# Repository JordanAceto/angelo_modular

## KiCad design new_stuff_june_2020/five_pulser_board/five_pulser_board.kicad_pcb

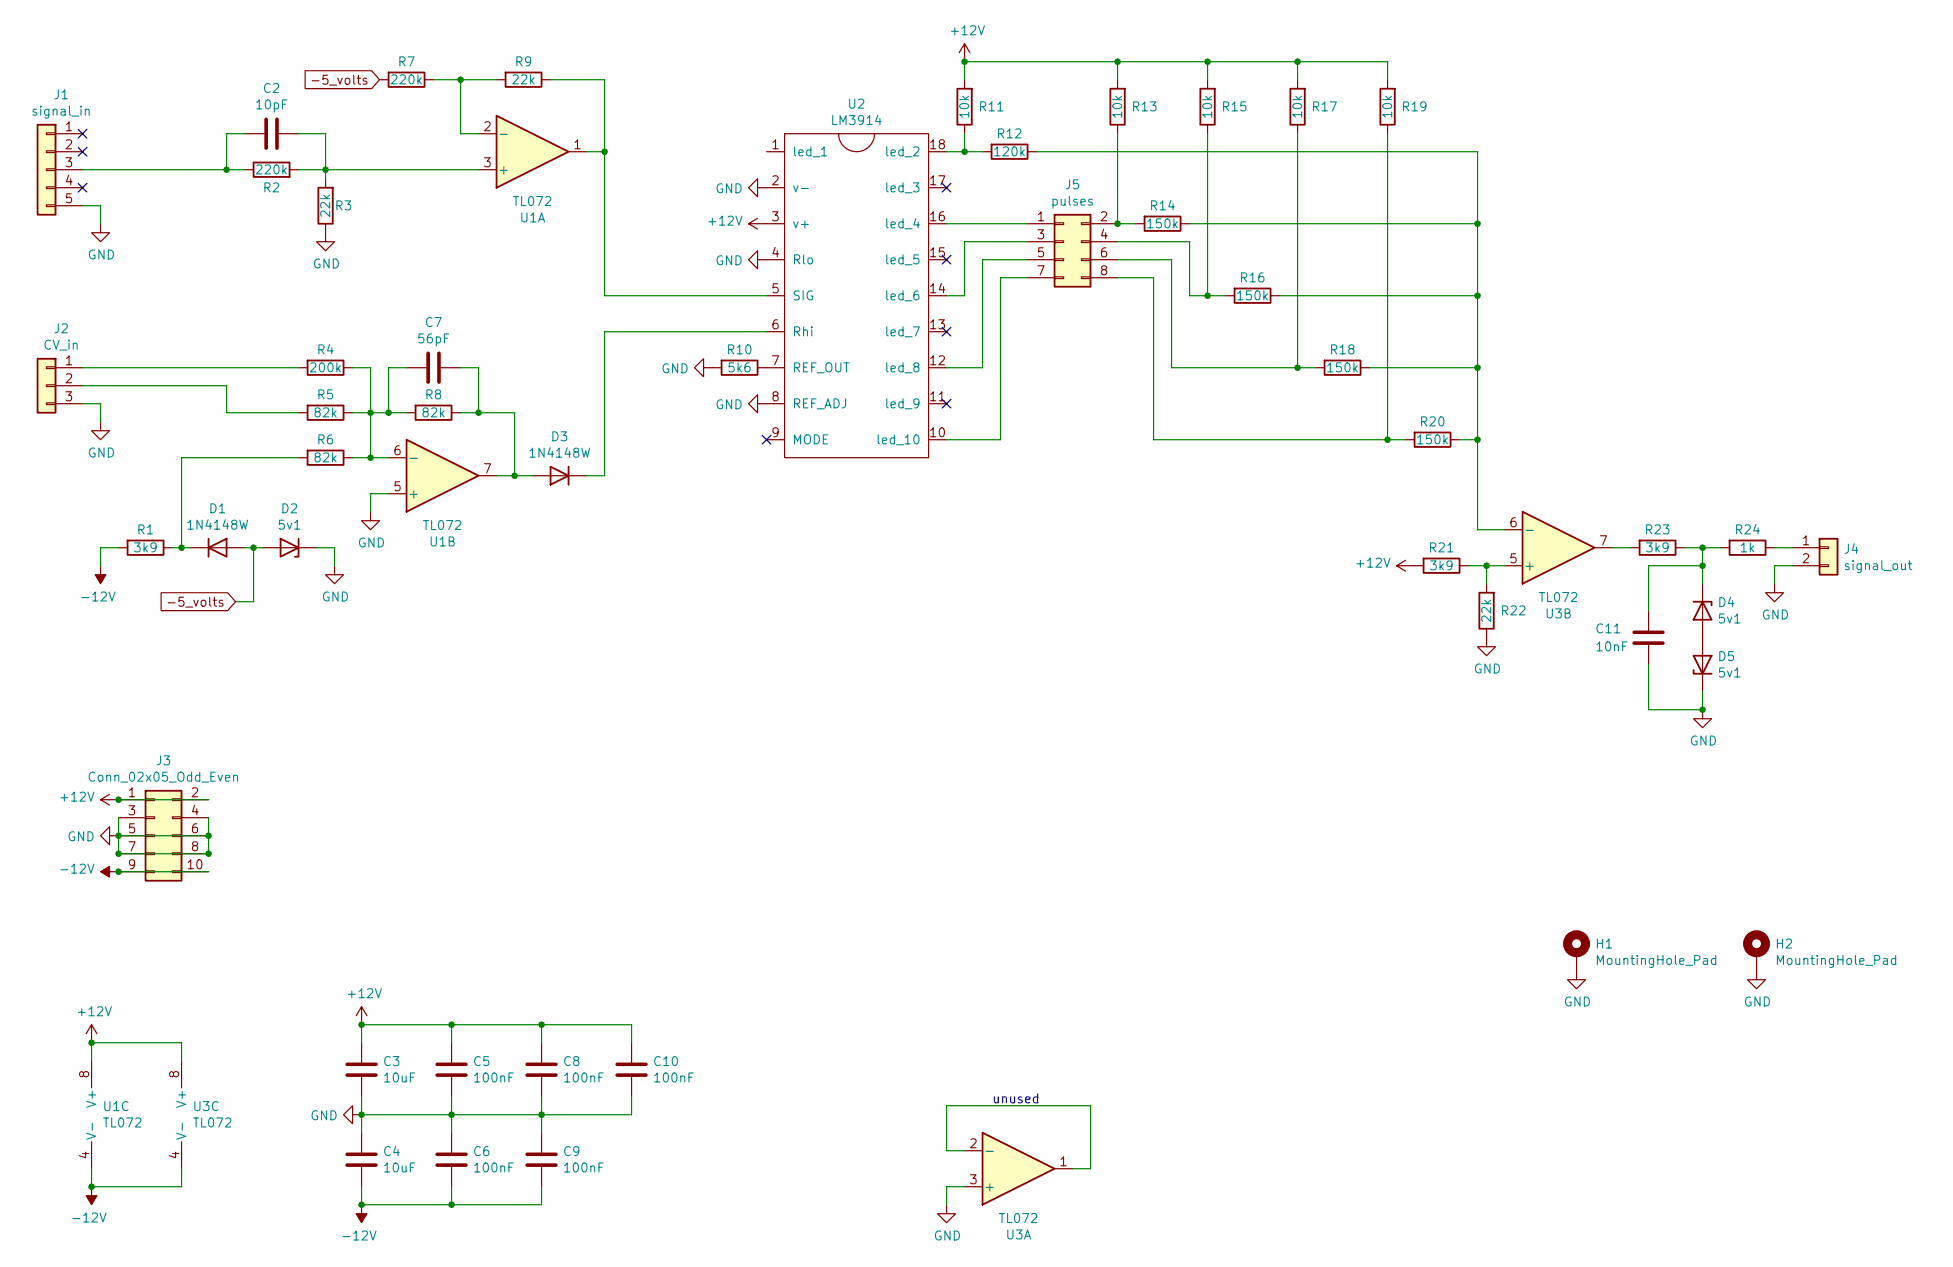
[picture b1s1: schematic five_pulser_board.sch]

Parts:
C2: 10pF; C_0805_2012Metric_Pad1.15x1.40mm_HandSolder
C3, C4: 10uF; C_0805_2012Metric_Pad1.15x1.40mm_HandSolder
C5, C6, C8, C9, C10: 100nF; C_0805_2012Metric_Pad1.15x1.40mm_HandSolder
C7: 56pF; C_0805_2012Metric_Pad1.15x1.40mm_HandSolder
C11: 10nF; C_0805_2012Metric_Pad1.15x1.40mm_HandSolder
D1, D3: 1N4148W; D_SOD-123
D2, D4, D5: 5v1; D_SOD-123
H1, H2: MountingHole_Pad; MountingHole_3.2mm_M3_Pad_Via
J1: signal_in; PinHeader_1x05_P2.54mm_Vertical
J2: CV_in; PinHeader_1x03_P2.54mm_Vertical
J3: Conn_02x05_Odd_Even; PinHeader_2x05_P2.54mm_Vertical
J4: signal_out; PinHeader_1x02_P2.54mm_Vertical
J5: pulses; PinHeader_2x04_P2.54mm_Vertical
R1, R21, R23: 3k9; R_0805_2012Metric_Pad1.15x1.40mm_HandSolder
R2, R7: 220k; R_0805_2012Metric_Pad1.15x1.40mm_HandSolder
R3, R9, R22: 22k; R_0805_2012Metric_Pad1.15x1.40mm_HandSolder
R4: 200k; R_0805_2012Metric_Pad1.15x1.40mm_HandSolder
R5, R6, R8: 82k; R_0805_2012Metric_Pad1.15x1.40mm_HandSolder
R10: 5k6; R_0805_2012Metric_Pad1.15x1.40mm_HandSolder
R11, R13, R15, R17, R19: 10k; R_0805_2012Metric_Pad1.15x1.40mm_HandSolder
R12: 120k; R_0805_2012Metric_Pad1.15x1.40mm_HandSolder
R14, R16, R18, R20: 150k; R_0805_2012Metric_Pad1.15x1.40mm_HandSolder
R24: 1k; R_0805_2012Metric_Pad1.15x1.40mm_HandSolder
U1, U3: TL072; SOIC-8_3.9x4.9mm_P1.27mm
U2: LM3914; DIP-18_W7.62mm

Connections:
+12V: C3.1, C5.1, C8.1, C10.1, J3.1, J3.2, R11.2, R13.2, R15.2, R17.2, R19.2, R21.2, U1.8 (V+), U2.3 (v+), U3.8 (V+)
-5_volts: D1.2 (A), D2.2 (A), R7.2
-12V: C4.2, C6.2, C9.2, J3.9, J3.10, R1.2, U1.4 (V-), U3.4 (V-)
GND: C3.2, C4.1, C5.2, C6.1, C8.2, C9.1, C10.2, C11.2, D2.1 (K), D5.1 (K), H1.1, H2.1, J1.5, J2.3, J3.3, J3.4, J3.5, J3.6, J3.7, J3.8, J4.2, R3.1, R10.2, R22.1, U1.5 (+), U2.2 (v-), U2.4 (Rlo), U2.8 (REF_ADJ), U3.3 (+)
unnamed: C2.1, R2.2, R3.2, U1.3 (+)
unnamed: C2.2, J1.3, R2.1
unnamed: C7.1, D3.2 (A), R8.1, U1.7
unnamed: C7.2, R4.1, R5.1, R6.1, R8.2, U1.6 (-)
unnamed: C11.1, D4.1 (K), R23.1, R24.2
unnamed: D1.1 (K), R1.1, R6.2
unnamed: D3.1 (K), U2.6 (Rhi)
unnamed: D4.2 (A), D5.2 (A)
unnamed: J2.1, R4.2
unnamed: J2.2, R5.2
unnamed: J4.1, R24.1
unnamed: J5.1, U2.16 (led_4)
unnamed: J5.2, R13.1, R14.2
unnamed: J5.3, U2.14 (led_6)
unnamed: J5.4, R15.1, R16.2
unnamed: J5.5, U2.12 (led_8)
unnamed: J5.6, R17.1, R18.2
unnamed: J5.7, U2.10 (led_10)
unnamed: J5.8, R19.1, R20.2
unnamed: R7.1, R9.2, U1.2 (-)
unnamed: R9.1, U1.1, U2.5 (SIG)
unnamed: R10.1, U2.7 (REF_OUT)
unnamed: R11.1, R12.2, U2.18 (led_2)
unnamed: R12.1, R14.1, R16.1, R18.1, R20.1, U3.6 (-)
unnamed: R21.1, R22.2, U3.5 (+)
unnamed: R23.2, U3.7
unnamed: U3.1, U3.2 (-)

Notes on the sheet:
unused

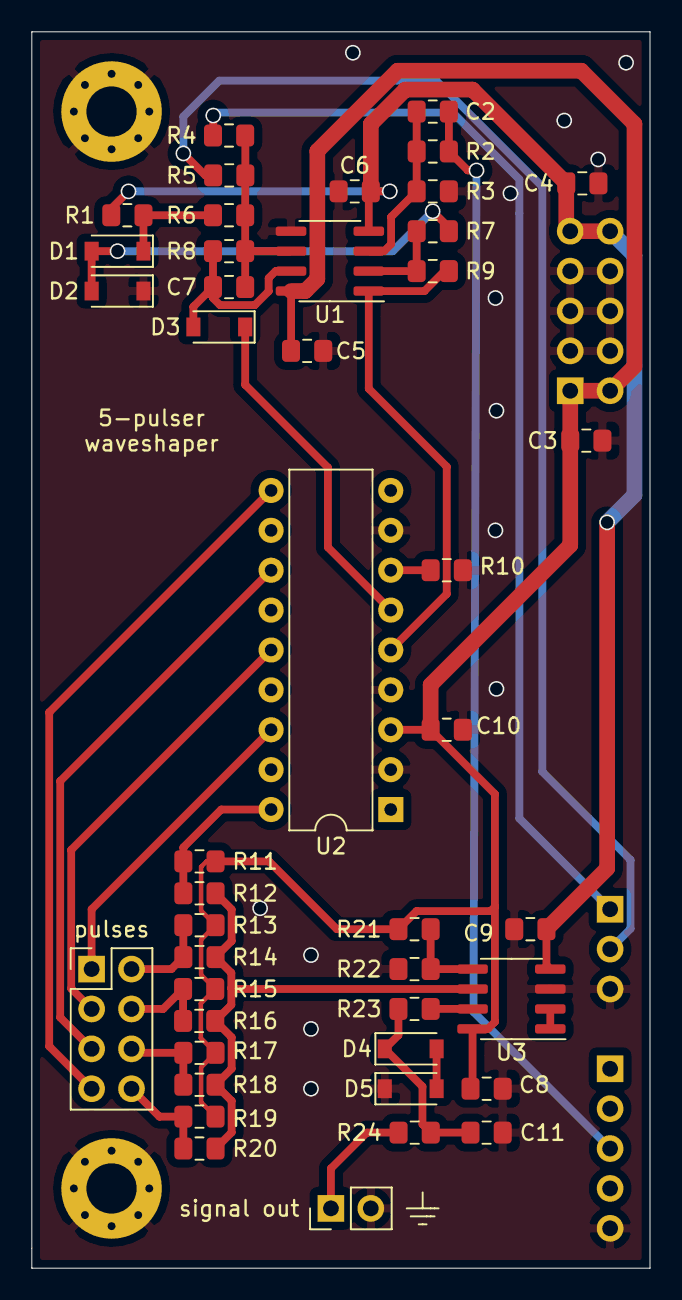
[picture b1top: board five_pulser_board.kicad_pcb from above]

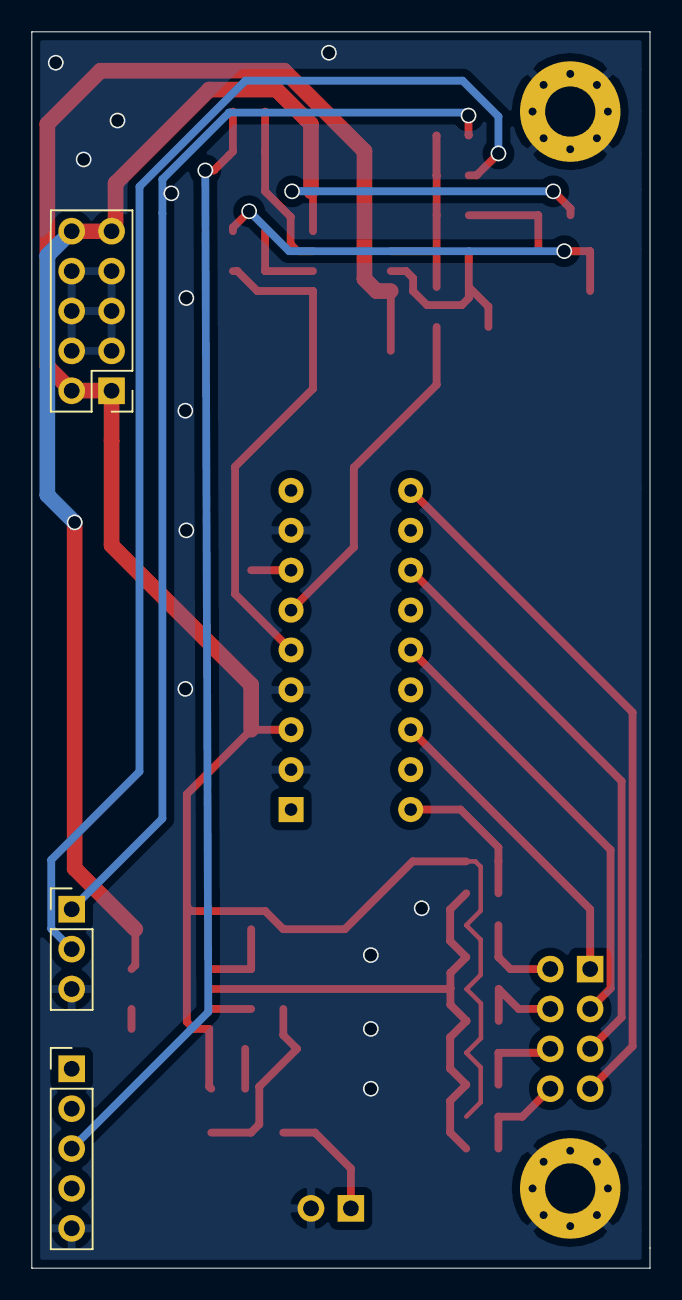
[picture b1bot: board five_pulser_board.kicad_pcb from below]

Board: 2 copper layers, 39.4 x 78.7 mm, 49 parts (3 on the bottom side), 31 nets.

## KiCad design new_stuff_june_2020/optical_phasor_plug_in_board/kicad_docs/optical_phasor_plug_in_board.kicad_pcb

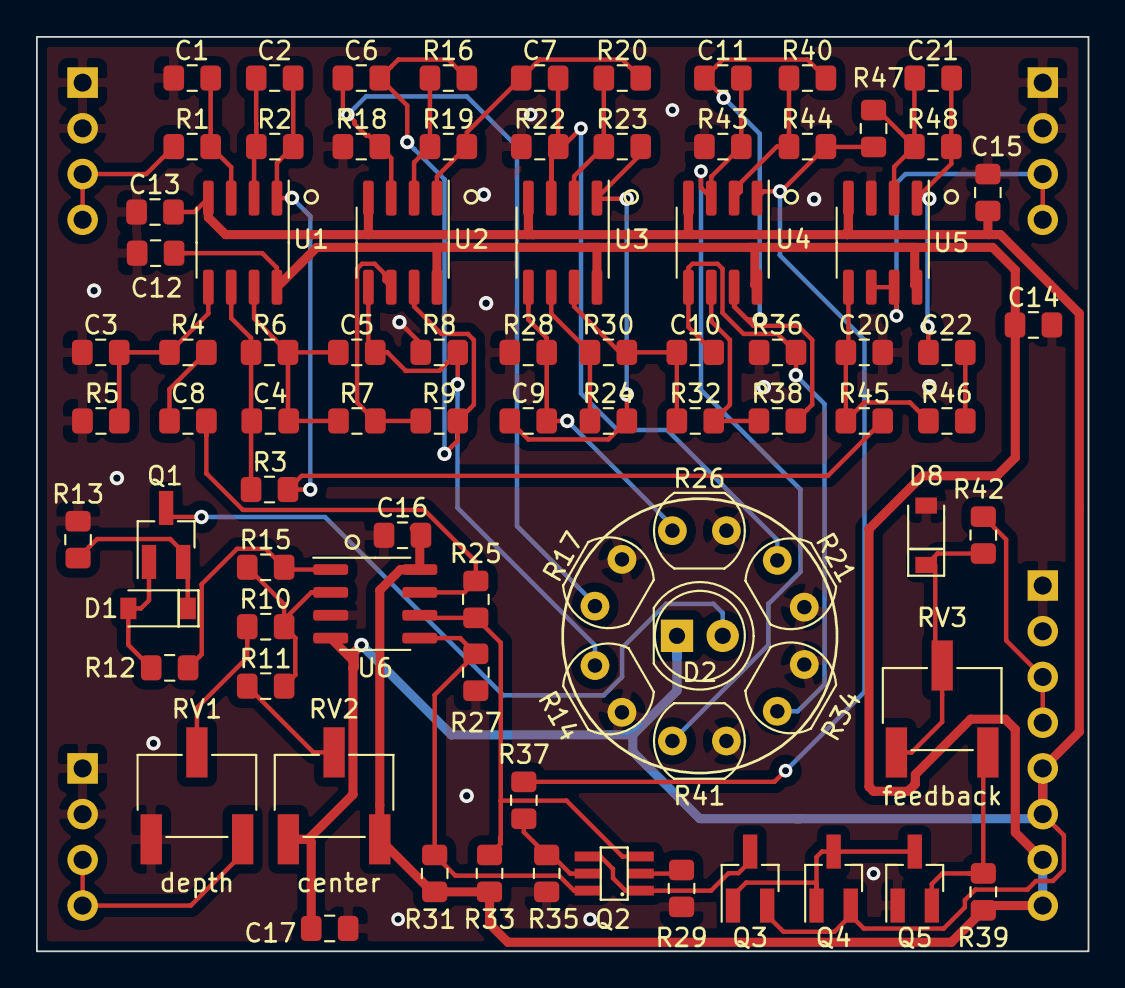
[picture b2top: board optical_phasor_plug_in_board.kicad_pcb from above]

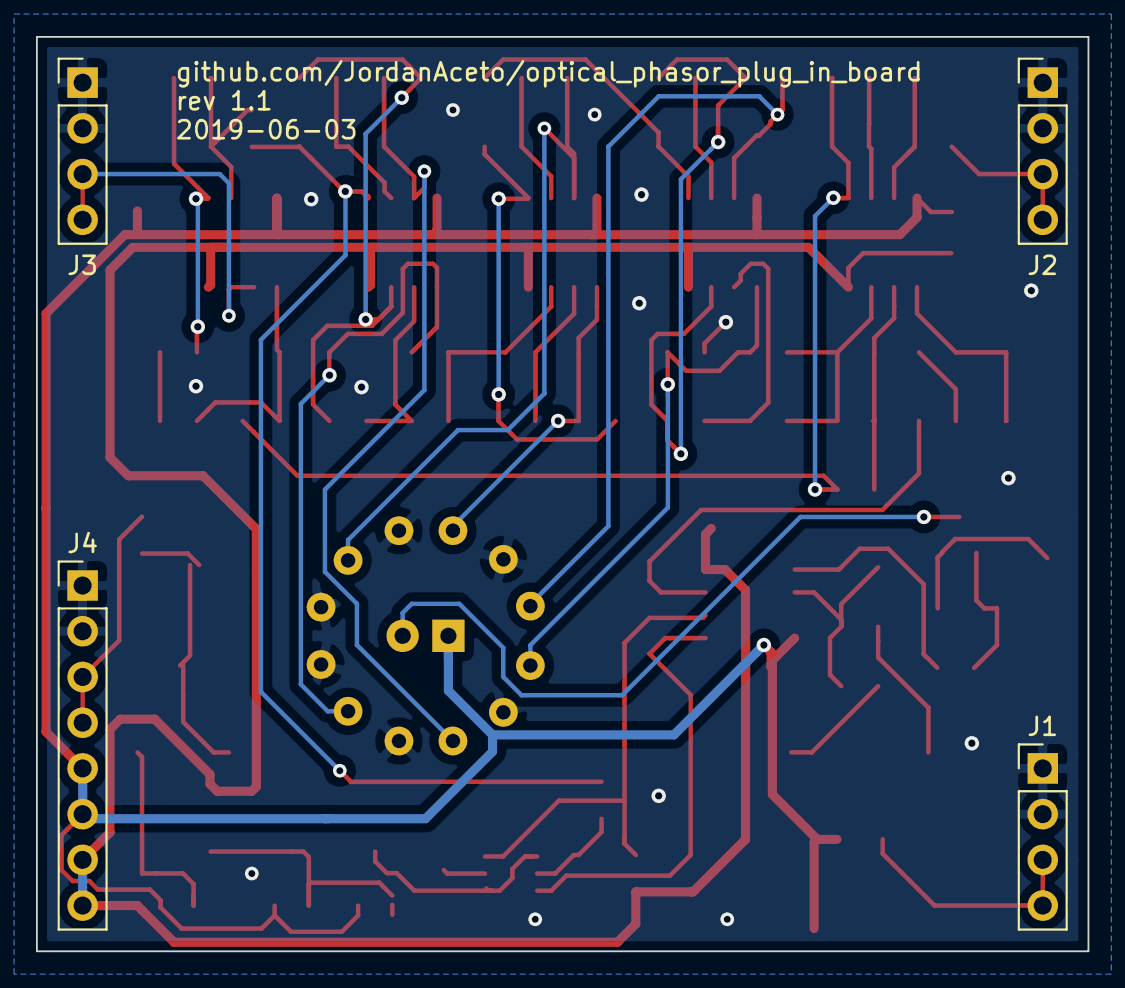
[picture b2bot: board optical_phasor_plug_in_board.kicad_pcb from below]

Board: 2 copper layers, 58.4 x 50.8 mm, 89 parts (4 on the bottom side), 52 nets.

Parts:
C1: 33pF; C_0805_2012Metric_Pad1.15x1.40mm_HandSolder
C2, C12, C13, C14, C15, C16, C17: 100nF; C_0805_2012Metric_Pad1.15x1.40mm_HandSolder
C3: 3n3; C_0805_2012Metric_Pad1.15x1.40mm_HandSolder
C4: 1nF; C_0805_2012Metric_Pad1.15x1.40mm_HandSolder
C5, C6, C7, C9, C10, C11: 6n8; C_0805_2012Metric_Pad1.15x1.40mm_HandSolder
C8: 470nF; C_0805_2012Metric_Pad1.15x1.40mm_HandSolder
C20: 470pF; C_0805_2012Metric_Pad1.15x1.40mm_HandSolder
C21: 1n; C_0805_2012Metric_Pad1.15x1.40mm_HandSolder
C22: 220nF; C_0805_2012Metric_Pad1.15x1.40mm_HandSolder
D1: 1N914; D_SOD-123
D2: green_diffused; LED_D5.0mm
D8: 1N5225B; D_SOD-123
J1, J2, J3: Conn_01x04_Male; PinHeader_1x04_P2.54mm_Vertical
J4: Conn_01x08_Male; PinHeader_1x08_P2.54mm_Vertical
Q1, Q5: MMBT3906; SOT-23_Handsoldering
Q2: BCM847DS135; SOT457
Q3, Q4: MMBT3904; SOT-23_Handsoldering
R1: 3k9; R_0805_2012Metric_Pad1.15x1.40mm_HandSolder
R2: 390k; R_0805_2012Metric_Pad1.15x1.40mm_HandSolder
R3, R6, R7, R9, R16, R19, R20, R23, R24, R30, R32, R38, R40, R44, R46, R47, R48: 4k7; R_0805_2012Metric_Pad1.15x1.40mm_HandSolder
R4: 8k2; R_0805_2012Metric_Pad1.15x1.40mm_HandSolder
R5, R8, R18, R22, R25, R27, R28, R36, R43: 220k; R_0805_2012Metric_Pad1.15x1.40mm_HandSolder
R10, R11, R13, R15: ???; R_0805_2012Metric_Pad1.15x1.40mm_HandSolder
R12: 10k; R_0805_2012Metric_Pad1.15x1.40mm_HandSolder
R14, R17, R21, R26, R34, R41: LDR; R_LDR_5.0x4.1mm_P3mm_Vertical
R29, R35: 220R; R_0805_2012Metric_Pad1.15x1.40mm_HandSolder
R31, R33: 47k; R_0805_2012Metric_Pad1.15x1.40mm_HandSolder
R37: 100k; R_0805_2012Metric_Pad1.15x1.40mm_HandSolder
R39: 680k; R_0805_2012Metric_Pad1.15x1.40mm_HandSolder
R42: 7k5; R_0805_2012Metric_Pad1.15x1.40mm_HandSolder
R45: 12k; R_0805_2012Metric_Pad1.15x1.40mm_HandSolder
RV1: 10k; Potentiometer_Bourns_3269W_Vertical
RV2: 100k; Potentiometer_Bourns_3269W_Vertical
RV3: 50k; Potentiometer_Bourns_3269W_Vertical
U1, U2, U3, U4, U5: RC4558; SOIC-8_3.9x4.9mm_P1.27mm
U6: TL072; SOIC-8_3.9x4.9mm_P1.27mm

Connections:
+12V: C12.1, C14.1, C16.1, J4.7, J4.8, R31.2, R33.2, R39.1, RV2.3, U1.8, U2.8, U3.8, U4.8, U5.8, U6.8
-12V: C13.1, C15.1, C17.1, D2.1, J4.5, J4.6, Q3.2, Q4.2, RV2.1, U1.4, U2.4, U3.4, U4.4, U5.4, U6.4
GND: C1.2, C3.2, C12.2, C13.2, C14.2, C15.2, C16.2, C17.2, C20.1, D8.2, J1.1, J1.2, J2.1, J2.2, J3.1, J3.2, J4.1, J4.2, Q5.1, R5.1, R8.1, R13.2, R14.2, R17.2, R18.1, R21.2, R22.1, R26.2, R27.1, R28.1, R29.1, R34.2, R35.1, R36.1, R41.2, R43.1, RV1.1, U5.3, U6.3
unnamed: C1.1, R1.2, U1.3
unnamed: C2.1, R2.1, R3.2, R45.2, U1.1
unnamed: C2.2, R2.2, U1.2
unnamed: C3.1, R4.2, R5.2, U1.5
unnamed: C4.1, R3.1, R6.2, U1.6
unnamed: C4.2, C5.2, R6.1, R7.2, U1.7
unnamed: C5.1, R8.2, R14.1, U2.5
unnamed: C6.1, R17.1, R18.2, U2.3
unnamed: C6.2, R9.1, R16.2, U2.7
unnamed: C7.1, R21.1, R22.2, U3.3
unnamed: C7.2, R19.1, R20.2, U2.1
unnamed: C8.1, R4.1
unnamed: C8.2, R25.1, U6.7
unnamed: C9.1, R26.1, R28.2, U3.5
unnamed: C9.2, R23.1, R24.2, U3.1
unnamed: C10.1, R34.1, R36.2, U4.5
unnamed: C10.2, R30.1, R32.2, U3.7
unnamed: C11.1, R41.1, R43.2, U4.3
unnamed: C11.2, R38.1, R40.2, U4.7
unnamed: C20.2, R45.1, R46.1, U5.5
unnamed: C21.1, C22.2, R48.1, U5.1
unnamed: C21.2, R47.1, R48.2, U5.2
unnamed: C22.1, R46.2
unnamed: D1.1, Q1.2, R13.1
unnamed: D1.2, Q1.1, R12.1
unnamed: D2.2, Q1.3
unnamed: D8.1, R42.1, RV3.1, RV3.2
unnamed: J1.3, J1.4, RV1.3
unnamed: J2.3, J2.4, R1.1
unnamed: J3.3, J3.4, U5.6, U5.7
unnamed: J4.3, J4.4, R42.2
unnamed: Q2.1, Q2.4, Q3.3
unnamed: Q2.2, R29.2
unnamed: Q2.3, R25.2, R33.1, U6.6
unnamed: Q2.5, R35.2, R37.1
unnamed: Q2.6, R27.2, R31.1, U6.5
unnamed: Q3.1, Q4.1, Q4.3, Q5.3
unnamed: Q5.2, R39.2, RV3.3
unnamed: R7.1, R9.2, U2.6
unnamed: R10.1, R11.1, R15.2, U6.2
unnamed: R10.2, RV1.2
unnamed: R11.2, RV2.2
unnamed: R12.2, R15.1, U6.1
unnamed: R16.1, R19.2, U2.2
unnamed: R20.1, R23.2, U3.2
unnamed: R24.1, R30.2, U3.6
unnamed: R32.1, R38.2, U4.6
unnamed: R37.2, R44.1, R47.2, U4.1
unnamed: R40.1, R44.2, U4.2

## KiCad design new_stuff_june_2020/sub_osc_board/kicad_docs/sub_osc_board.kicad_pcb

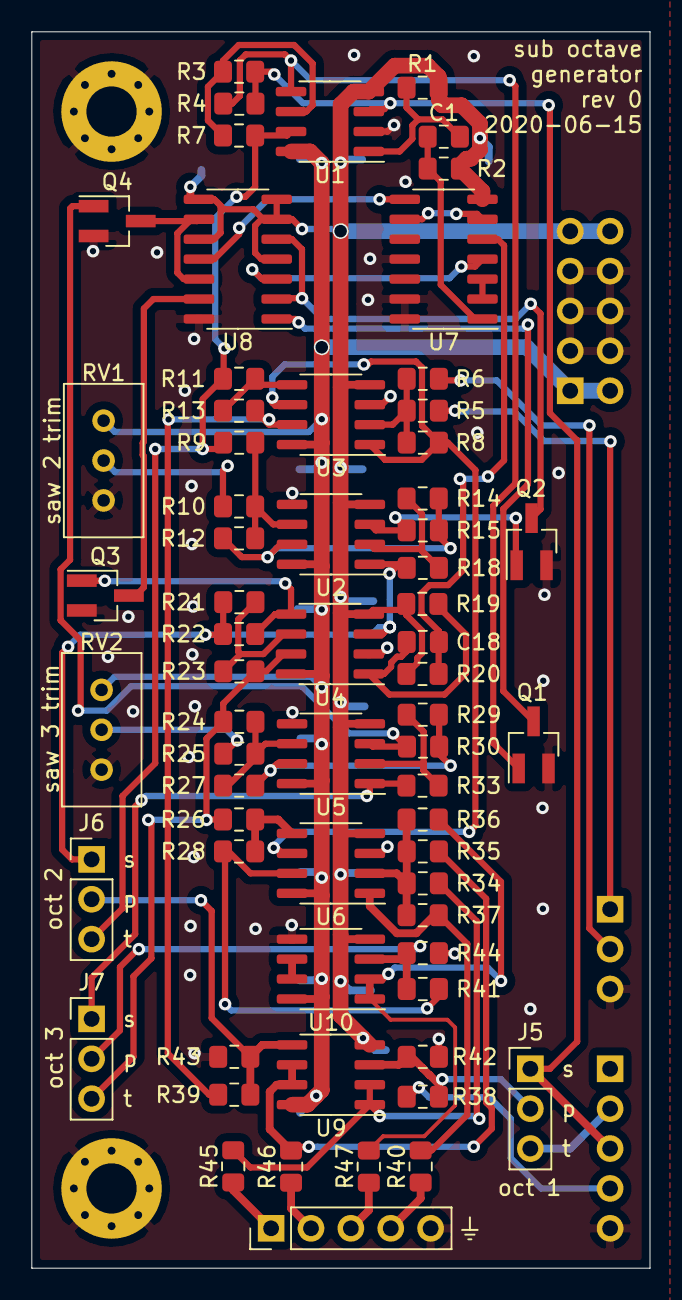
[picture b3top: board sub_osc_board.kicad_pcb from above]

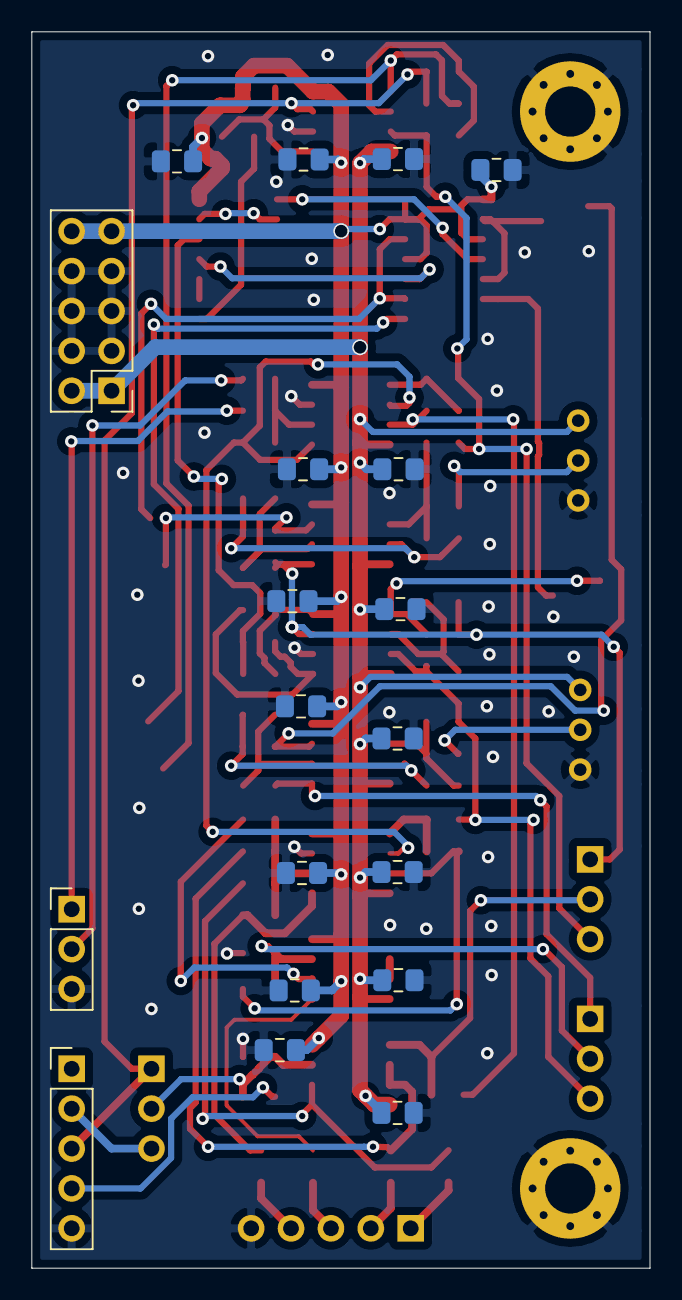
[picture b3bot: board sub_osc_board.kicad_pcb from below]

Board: 2 copper layers, 39.4 x 78.7 mm, 86 parts (19 on the bottom side), 57 nets.

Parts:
C1, C18: 1nF; C_0805_2012Metric_Pad1.15x1.40mm_HandSolder
C2, C3, C4, C5, C6, C7, C8, C9, C10, C11, C12, C13, C14, C15: 100nF; C_0805_2012Metric_Pad1.15x1.40mm_HandSolder
C16, C17: 10uF; C_0805_2012Metric_Pad1.15x1.40mm_HandSolder
H1, H2: MountingHole_Pad; MountingHole_3.2mm_M3_Pad_Via
J1: signal_inputs; PinHeader_1x05_P2.54mm_Vertical
J2: pwm_inputs; PinHeader_1x03_P2.54mm_Vertical
J3: power_input; PinHeader_2x05_P2.54mm_Vertical
J4: signal_outputs; PinHeader_1x05_P2.54mm_Vertical
J5, J6, J7: Conn_01x03; PinHeader_1x03_P2.54mm_Vertical
Q1, Q2, Q3, Q4: MMBF5457; SOT-23_Handsoldering
R1, R19: 10k; R_0805_2012Metric_Pad1.15x1.40mm_HandSolder
R2, R20: 22k; R_0805_2012Metric_Pad1.15x1.40mm_HandSolder
R3, R4, R6, R7, R9, R10, R14, R15, R18, R21, R22, R23, R24, R25, R29, R30, R33, R34, R35, R36, R37, R43, R44: 100k; R_0805_2012Metric_Pad1.15x1.40mm_HandSolder
R5: 330k; R_0805_2012Metric_Pad1.15x1.40mm_HandSolder
R8: 150k; R_0805_2012Metric_Pad1.15x1.40mm_HandSolder
R11, R26: 2k2; R_0805_2012Metric_Pad1.15x1.40mm_HandSolder
R12, R27: 51k; R_0805_2012Metric_Pad1.15x1.40mm_HandSolder
R13, R28: 2M2; R_0805_2012Metric_Pad1.15x1.40mm_HandSolder
R38, R39, R41: 120k; R_0805_2012Metric_Pad1.15x1.40mm_HandSolder
R40, R45, R46, R47: 1k; R_0805_2012Metric_Pad1.15x1.40mm_HandSolder
R42: dnf; R_0805_2012Metric_Pad1.15x1.40mm_HandSolder
RV1, RV2: 100k; Potentiometer_Bourns_3296W_Vertical
U1, U2, U3, U4, U5, U6, U9, U10: TL072; SOIC-8_3.9x4.9mm_P1.27mm
U7: 40106; SOIC-14_3.9x8.7mm_P1.27mm
U8: 4013; SOIC-14_3.9x8.7mm_P1.27mm

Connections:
+12V: C4.1, C6.1, C8.1, C10.1, C12.1, C14.1, C16.1, J3.1, J3.2, RV1.1, RV2.1, U1.8, U2.8, U3.8, U4.8, U5.8, U6.8, U9.8, U10.8
-12V: C2.2, C3.2, C5.2, C7.2, C9.2, C11.2, C13.2, C15.2, C17.2, J3.9, J3.10, R1.2, R2.2, R19.2, R20.2, U1.4, U2.4, U3.4, U4.4, U5.4, U6.4, U7.7, U8.4, U8.6, U8.7, U8.8, U8.10, U9.4, U10.4
/base_oct_out: R34.2, R45.2, U9.1, U9.2
/mix_out: R37.1, R40.2, U6.1
/pulse_in: J1.4, R38.2
/pulse_over_2: R13.1, R39.2, U3.7
/pulse_over_4: R28.1, R41.2, U6.7
/saw_in: J1.3, J5.1, R3.2, R4.2, U1.3
/saw_over_2: J6.1, R18.1, R21.2, R22.2, U2.1, U4.3
/saw_over_4: J7.1, R33.1, U5.1
/sub_oct_1_out: R35.2, R46.2, U9.6, U9.7
/sub_oct_2_out: R36.2, R47.2, U10.1, U10.2
/sub_osc_1/man_pw_in_1: J2.1, R5.2
/sub_osc_1/pwm_in_1: J2.2, R6.2
/sub_osc_1/summed_PWM: R8.1, U3.1, U3.6, U6.6
/tri_in: J1.2, J5.3
/tri_over_2: J6.3, R7.1, R9.2, R11.2, U1.7
/tri_over_4: J7.3, R23.1, R24.2, R26.2, U4.7
GND: C2.1, C3.1, C4.2, C5.1, C6.2, C7.1, C8.2, C9.1, C10.2, C11.1, C12.2, C13.1, C14.2, C15.1, C16.2, C17.1, H1.1, H2.1, J1.5, J2.3, J3.3, J3.4, J3.5, J3.6, J3.7, J3.8, J4.5, Q1.2, Q2.2, Q3.2, Q4.2, R42.2, R43.2, R44.2, RV1.3, RV2.3, U1.2, U2.5, U3.3, U4.2, U5.5, U6.3, U7.11, U7.13, U7.14, U8.14, U10.5
unnamed: C1.1, R2.1, U7.1
unnamed: C1.2, R1.1, U1.1
unnamed: C18.1, R20.1, U7.5
unnamed: C18.2, R19.1, U4.1
unnamed: J4.1, R45.1
unnamed: J4.2, R46.1
unnamed: J4.3, R47.1
unnamed: J4.4, R40.1
unnamed: J5.2, R38.1, R42.1, U9.3
unnamed: J6.2, R39.1, R43.1, U9.5
unnamed: J7.2, R41.1, R44.1, U10.3
unnamed: Q1.1, R4.1, U1.5
unnamed: Q1.3, U8.1
unnamed: Q2.1, R15.1, U2.3
unnamed: Q2.3, U8.2, U8.5
unnamed: Q3.1, R22.1, U4.5
unnamed: Q3.3, U8.13
unnamed: Q4.1, R30.1, U5.3
unnamed: Q4.3, U8.9, U8.12
unnamed: R3.1, R7.2, U1.6
unnamed: R5.1, R6.1, R8.2, U3.2
unnamed: R9.1, R10.1, R12.2, U2.6
unnamed: R10.2, RV1.2
unnamed: R11.1, R13.2, U3.5
unnamed: R12.1, R14.2, R15.2, U2.7
unnamed: R14.1, R18.2, U2.2
unnamed: R21.1, R23.2, U4.6
unnamed: R24.1, R25.1, R27.2, U5.6
unnamed: R25.2, RV2.2
unnamed: R26.1, R28.2, U6.5
unnamed: R27.1, R29.2, R30.2, U5.7
unnamed: R29.1, R33.2, U5.2
unnamed: R34.1, R35.1, R36.1, R37.2, U6.2
unnamed: U7.2, U7.3
unnamed: U7.4, U8.3
unnamed: U7.6, U7.9
unnamed: U7.8, U8.11
unnamed: U10.6, U10.7

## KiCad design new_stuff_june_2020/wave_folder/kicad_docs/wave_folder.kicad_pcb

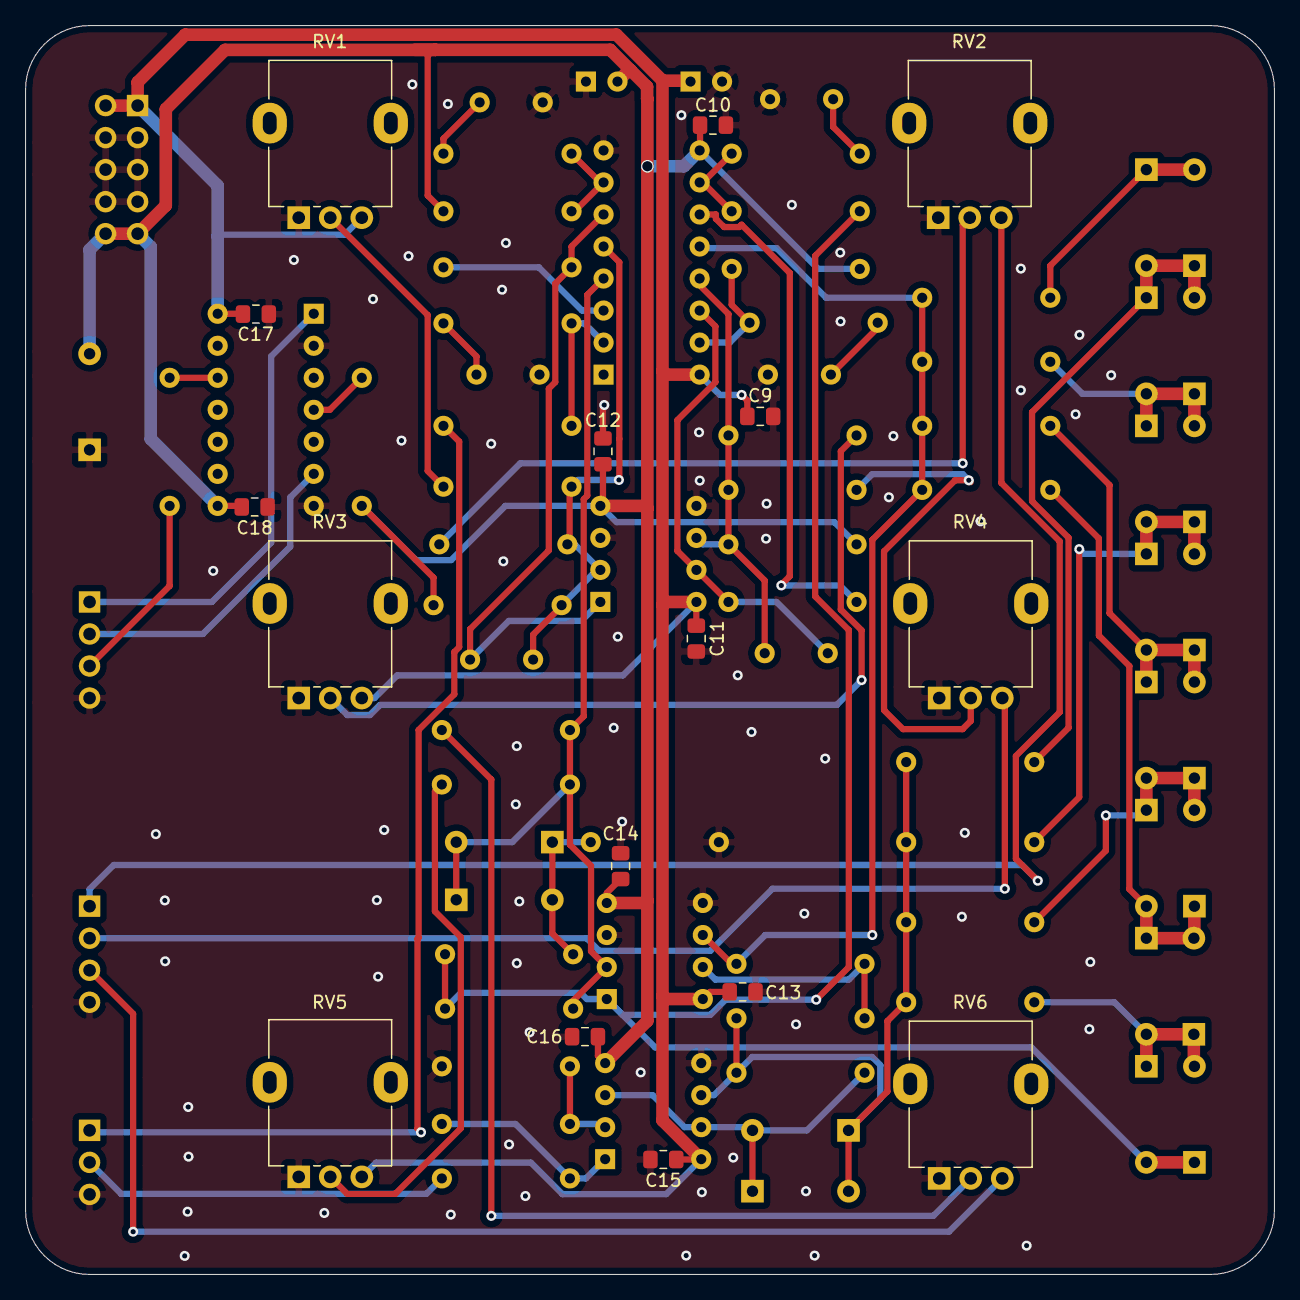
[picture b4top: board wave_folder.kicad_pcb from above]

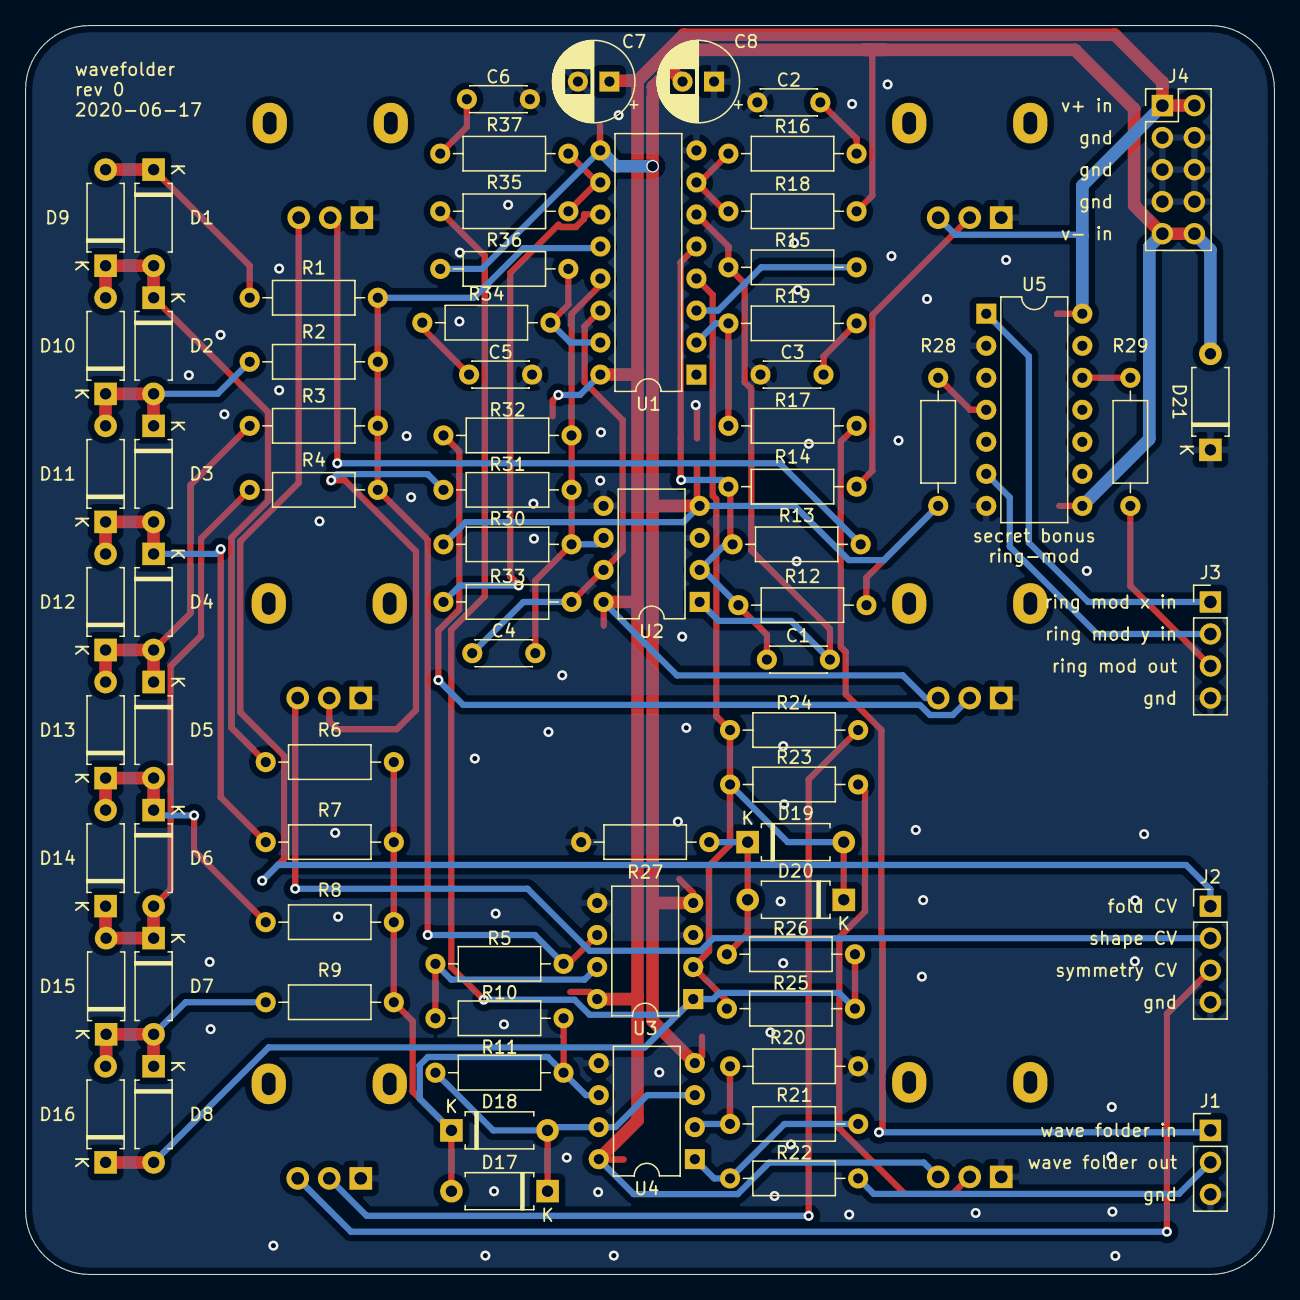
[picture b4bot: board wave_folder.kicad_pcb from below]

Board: 2 copper layers, 99.1 x 99.1 mm, 91 parts (75 on the bottom side), 50 nets.

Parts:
C1, C4: 100pF; C_Disc_D4.3mm_W1.9mm_P5.00mm
C2, C3, C5, C6: 560pF; C_Disc_D4.3mm_W1.9mm_P5.00mm
C7, C8: 10uF; CP_Radial_D6.3mm_P2.50mm
C9, C10, C11, C12, C13, C14, C15, C16, C17, C18: 100nF; C_0805_2012Metric_Pad1.15x1.40mm_HandSolder
D1, D2, D3, D4, D5, D6, D7, D8, D9, D10, D11, D12, D13, D14, D15, D16, D17, D18, D19, D20: D; D_A-405_P7.62mm_Horizontal
D21: D_Schottky; D_A-405_P7.62mm_Horizontal
J1: signal_port; PinHeader_1x03_P2.54mm_Vertical
J2: CV_port; PinHeader_1x04_P2.54mm_Vertical
J3: ring_mod_port; PinHeader_1x04_P2.54mm_Vertical
J4: power_in_connector; PinHeader_2x05_P2.54mm_Vertical
R1, R2, R3, R4, R6, R7, R8, R9: 15k; R_Axial_DIN0207_L6.3mm_D2.5mm_P10.16mm_Horizontal
R5, R10, R28: 5k6; R_Axial_DIN0207_L6.3mm_D2.5mm_P10.16mm_Horizontal
R11, R21: 56k; R_Axial_DIN0207_L6.3mm_D2.5mm_P10.16mm_Horizontal
R12, R30: 10M; R_Axial_DIN0207_L6.3mm_D2.5mm_P10.16mm_Horizontal
R13, R17, R24, R31: 100k; R_Axial_DIN0207_L6.3mm_D2.5mm_P10.16mm_Horizontal
R14, R23, R32: 220k; R_Axial_DIN0207_L6.3mm_D2.5mm_P10.16mm_Horizontal
R15, R33: 4k7; R_Axial_DIN0207_L6.3mm_D2.5mm_P10.16mm_Horizontal
R16, R19, R34, R37: 510; R_Axial_DIN0207_L6.3mm_D2.5mm_P10.16mm_Horizontal
R18, R36: 240k; R_Axial_DIN0207_L6.3mm_D2.5mm_P10.16mm_Horizontal
R20: 7k5; R_Axial_DIN0207_L6.3mm_D2.5mm_P10.16mm_Horizontal
R22, R29: 1k; R_Axial_DIN0207_L6.3mm_D2.5mm_P10.16mm_Horizontal
R25: 180k; R_Axial_DIN0207_L6.3mm_D2.5mm_P10.16mm_Horizontal
R26: 33k; R_Axial_DIN0207_L6.3mm_D2.5mm_P10.16mm_Horizontal
R27: 2k7; R_Axial_DIN0207_L6.3mm_D2.5mm_P10.16mm_Horizontal
R35: 27k; R_Axial_DIN0207_L6.3mm_D2.5mm_P10.16mm_Horizontal
RV1, RV2, RV3, RV4, RV5, RV6: 100k; Potentiometer_Alpha_RD901F-40-00D_Single_Vertical
U1: SSM2164; DIP-16_W7.62mm
U2, U3, U4: TL072; DIP-8_W7.62mm
U5: AD534; DIP-14_W7.62mm

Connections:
+12V: C7.1, C9.1, C11.1, C13.1, C15.1, C17.1, J4.1, J4.2, RV1.3, RV3.3, RV5.3, U1.16, U2.8, U3.8, U4.8, U5.14
-12V: C8.2, C10.2, C12.2, C14.2, C16.2, C18.2, D21.2, J4.9, J4.10, R12.2, R18.1, R28.2, R30.2, R36.1, U1.9, U2.4, U3.4, U4.4, U5.8
/core/core_i_in: R1.2, R2.2, R3.2, R4.2, R5.2, U1.12, U3.6
/core/core_out: D17.1, D18.2, R11.1, U4.3, U4.7
/core/core_v_in: D8.2, D16.1, R25.1, R26.1, R35.2, U3.1
/folds_CV: R13.2, RV2.2
/folds_CV_in: J2.1, RV2.3
/folds_VCA/folds_VCA_signal_i_out: D19.2, D20.1, R23.1, R24.1, R25.2, U1.4, U3.2
/manual_folds: R14.2, RV1.2
/manual_shape: R32.2, RV3.2
/manual_symmetry: R23.2, RV5.2
/ring_mod_out: J3.3, R29.1
/ring_mod_x_in: J3.1, U5.1
/ring_mod_y_in: J3.2, U5.6
/shape_CV: R31.2, RV4.2
/shape_CV_in: J2.2, RV4.3
/signal_in: J1.1, R17.2
/signal_out: J1.2, R22.2
/symmetry_CV: R24.2, RV6.2
/symmetry_CV_in: J2.3, RV6.3
GND: C2.2, C3.2, C5.2, C6.2, C7.2, C8.1, C9.2, C10.1, C11.2, C12.1, C13.2, C14.1, C15.2, C16.1, C17.2, C18.1, D21.1, J1.3, J2.4, J3.4, J4.3, J4.4, J4.5, J4.6, J4.7, J4.8, R20.1, R27.2, RV1.1, RV2.1, RV3.1, RV4.1, RV5.1, RV6.1, U1.8, U2.3, U2.5, U3.3, U3.5, U4.5, U5.2, U5.7
unnamed: C1.1, R15.2, U1.6, U2.1
unnamed: C1.2, R12.1, R13.1, R14.1, U1.5, U2.2
unnamed: C2.1, R16.1
unnamed: C3.1, R19.1
unnamed: C4.1, R33.2, U1.14, U2.7
unnamed: C4.2, R30.1, R31.1, R32.1, U1.13, U2.6
unnamed: C5.1, R34.1
unnamed: C6.1, R37.1
unnamed: D1.1, D9.2, R1.1
unnamed: D1.2, D2.1, D9.1, D10.2, R6.2
unnamed: D2.2, D3.1, D10.1, D11.2, R2.1
unnamed: D3.2, D4.1, D11.1, D12.2, R7.2
unnamed: D4.2, D5.1, D12.1, D13.2, R3.1
unnamed: D5.2, D6.1, D13.1, D14.2, R8.2
unnamed: D6.2, D7.1, D14.1, D15.2, R4.1
unnamed: D7.2, D8.1, D15.1, D16.2, R9.2
unnamed: D17.2, D18.1, R6.1, R7.1, R8.1, R9.1, R10.1, R11.2, U4.6
unnamed: D19.1, D20.2, R26.2, R27.1
unnamed: R5.1, R10.2, U3.7
unnamed: R15.1, U1.3
unnamed: R16.2, R18.2, U1.7
unnamed: R17.1, R19.2, U1.2
unnamed: R20.2, R21.1, U4.2
unnamed: R21.2, R22.1, U4.1
unnamed: R28.1, U5.4
unnamed: R29.2, U5.12
unnamed: R33.1, U1.11
unnamed: R34.2, R36.2, U1.15
unnamed: R35.1, R37.2, U1.10

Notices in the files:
new_stuff_june_2020/optical_phasor_plug_in_board/kicad_docs/optical_phasor_plug_in_board.kicad_pcb:
Licinse: CC by 4.0
oscillator_carrier_board/kicad_docs/oscillator_carrier_board.kicad_pcb:
License: CC by 4.0
